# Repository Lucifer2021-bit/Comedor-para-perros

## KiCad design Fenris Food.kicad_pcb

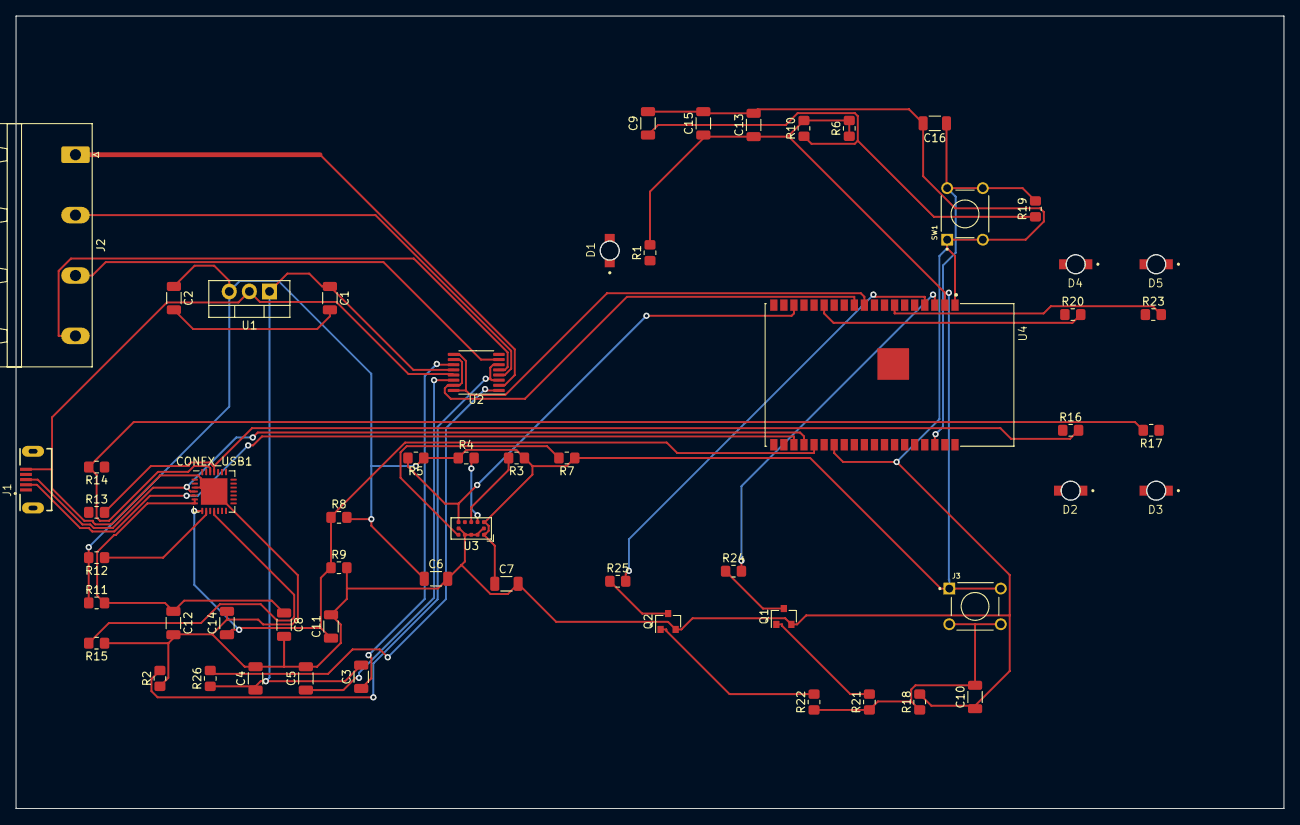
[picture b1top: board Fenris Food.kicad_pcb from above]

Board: 2 copper layers, 160.0 x 100.0 mm, 58 parts (0 on the bottom side), 37 nets.

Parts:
C1: 0.33uF; C_1206_3216Metric
C2, C9, C10, C12, C14, C16: 0.1uF; C_1206_3216Metric
C3: 0.01uF; C_1206_3216Metric
C4: 10uF?; C_1206_3216Metric
C5: 2.2uF; C_1206_3216Metric
C6, C13: 100uF; C_1206_3216Metric
C7: 4.7uF; C_1206_3216Metric
C8, C11: 10uF; C_1206_3216Metric
C15: 1uF; C_1206_3216Metric
CONEX_USB1: CP2102N-A01-GQFN28; QFN-28-1EP_5x5mm_P0.5mm_EP3.35x3.35mm
D1, D2, D3, D4, D5: LED; LED_SMD_S124A
J1: USB_B_Micro; GCT_USB3140-30-0230-1-C_REVE1
J2: Screw_Terminal_01x04; PhoenixContact_GMSTBA_2,5_4-G-7,62_1x04_P7.62mm_Horizontal
J3: Conn_02x02_Top_Bottom; PULSEBUTTON
Q1, Q2: BSS138; SOT-23
R1, R20, R23: 330; R_0805_2012Metric_Pad1.20x1.40mm_HandSolder
R2: 200m; R_0805_2012Metric_Pad1.20x1.40mm_HandSolder
R3, R4, R6, R10, R18: 10K; R_0805_2012Metric_Pad1.20x1.40mm_HandSolder
R5, R7, R26: 47K; R_0805_2012Metric_Pad1.20x1.40mm_HandSolder
R8: 22.1K; R_0805_2012Metric_Pad1.20x1.40mm_HandSolder
R9: 47.5K; R_0805_2012Metric_Pad1.20x1.40mm_HandSolder
R11: 5; R_0805_2012Metric_Pad1.20x1.40mm_HandSolder
R12, R16, R17: 2K; R_0805_2012Metric_Pad1.20x1.40mm_HandSolder
R13, R14, R15: 10k; R_0805_2012Metric_Pad1.20x1.40mm_HandSolder
R19, R21, R22: 1K; R_0805_2012Metric_Pad1.20x1.40mm_HandSolder
R24, R25: R; R_0805_2012Metric_Pad1.20x1.40mm_HandSolder
SW1: SW_Push_LED; PULSEBUTTON
U1: LM7812_TO220; TO-220-3_Vertical
U2: DRV8833PW; TSSOP-16_4.4x5mm_P0.65mm
U3: VL53L1CXV0FY1; ST_VL53L1x
U4: ESP32-S2-WROVER; ESP32-WROVER-B

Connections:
+3V3: C2.1, C6.1, C7.1, C13.1, C15.1, J3.1, J3.2, R1.2, R3.1, R4.1, R5.1, R6.1, R6.2, R7.1, R8.2, R10.2, R11.1, R12.2, U1.3, U3.1, U3.11, U4.2
+5V: C1.1, C3.2, C4.1, R26.1, U1.1, U2.12
/Comunicacion/CONTROL: R20.2, U4.14
/Comunicacion/D+_USB: CONEX_USB1.4, J1.3, U4.23
/Comunicacion/D-_USB: CONEX_USB1.5, J1.2, U4.22
/Comunicacion/EN: C9.1, R10.1, R19.1
/Comunicacion/ESP_RST: C16.1, R19.2, SW1.2, SW1.4, U4.36
/Comunicacion/GPIO1: R5.2, U3.7, U4.17
/Comunicacion/IN1: U2.9, U2.16, U4.10
/Comunicacion/IN2: U2.10, U2.15, U4.11
/Comunicacion/IO0: R24.2, U4.3
/Comunicacion/IO1: R25.2, U4.4
/Comunicacion/IO4: R23.2, U4.7
/Comunicacion/REGIN: C8.1, C12.1, CONEX_USB1.6, CONEX_USB1.7, R11.2
/Comunicacion/RXD: CONEX_USB1.25, R13.2, R16.2
/Comunicacion/TXD: CONEX_USB1.26, R14.2, R17.2
/Comunicacion/VBUS_TX: C11.1, C14.1, CONEX_USB1.8, R8.1, R9.1, U4.24
/VCC/MTR1: J2.1, U2.2
/VCC/MTR2: J2.2, U2.4
/VCC/MTR3: J2.3, U2.7
/VCC/MTR4: J2.4, U2.5
/VCC/SCL: R4.2, U3.10
/VCC/SDA: R3.2, U3.9
/VCC/XSHUT: R7.2, U3.5
GND: C4.2, C5.2, C6.2, C7.2, C8.2, C9.2, C10.1, C11.2, C12.2, C13.2, C14.2, C15.2, C16.2, CONEX_USB1.3, CONEX_USB1.29, J1.5, Q1.2, Q2.2, R2.1, R9.2, R15.1, R18.2, SW1.1, SW1.3, U1.2, U2.13, U3.2, U3.3, U3.4, U3.6, U3.12, U4.1, U4.26
unnamed: C1.2, C2.2
unnamed: C3.1, U2.11
unnamed: C5.1, U2.14
unnamed: C10.2, J3.3, J3.4, R18.1, R21.1, R22.1
unnamed: CONEX_USB1.9, R12.1
unnamed: CONEX_USB1.11, R15.2
unnamed: Q1.1, R21.2
unnamed: Q1.3, R24.1
unnamed: Q2.1, R22.2
unnamed: Q2.3, R25.1
unnamed: R2.2, U2.3, U2.6
unnamed: R26.2, U2.1
